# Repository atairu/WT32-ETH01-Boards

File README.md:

KiCAD files for WT32-ETH01 MCU breakout board PCBs. PCBs includes

* 1-Port with USB 2.0 receptacle
* 1-Port with USB type C receptacle
* 2-Port with USB 2.0 receptacle
* 4-Port with USB 2.0 receptacle
* 8-Port with USB 2.0 receptacle

The boards feature multi voltage on the input between 5v - 24v and can be used to program WT32-ETH01 using on-board serial to UART protocol IC with WLED.

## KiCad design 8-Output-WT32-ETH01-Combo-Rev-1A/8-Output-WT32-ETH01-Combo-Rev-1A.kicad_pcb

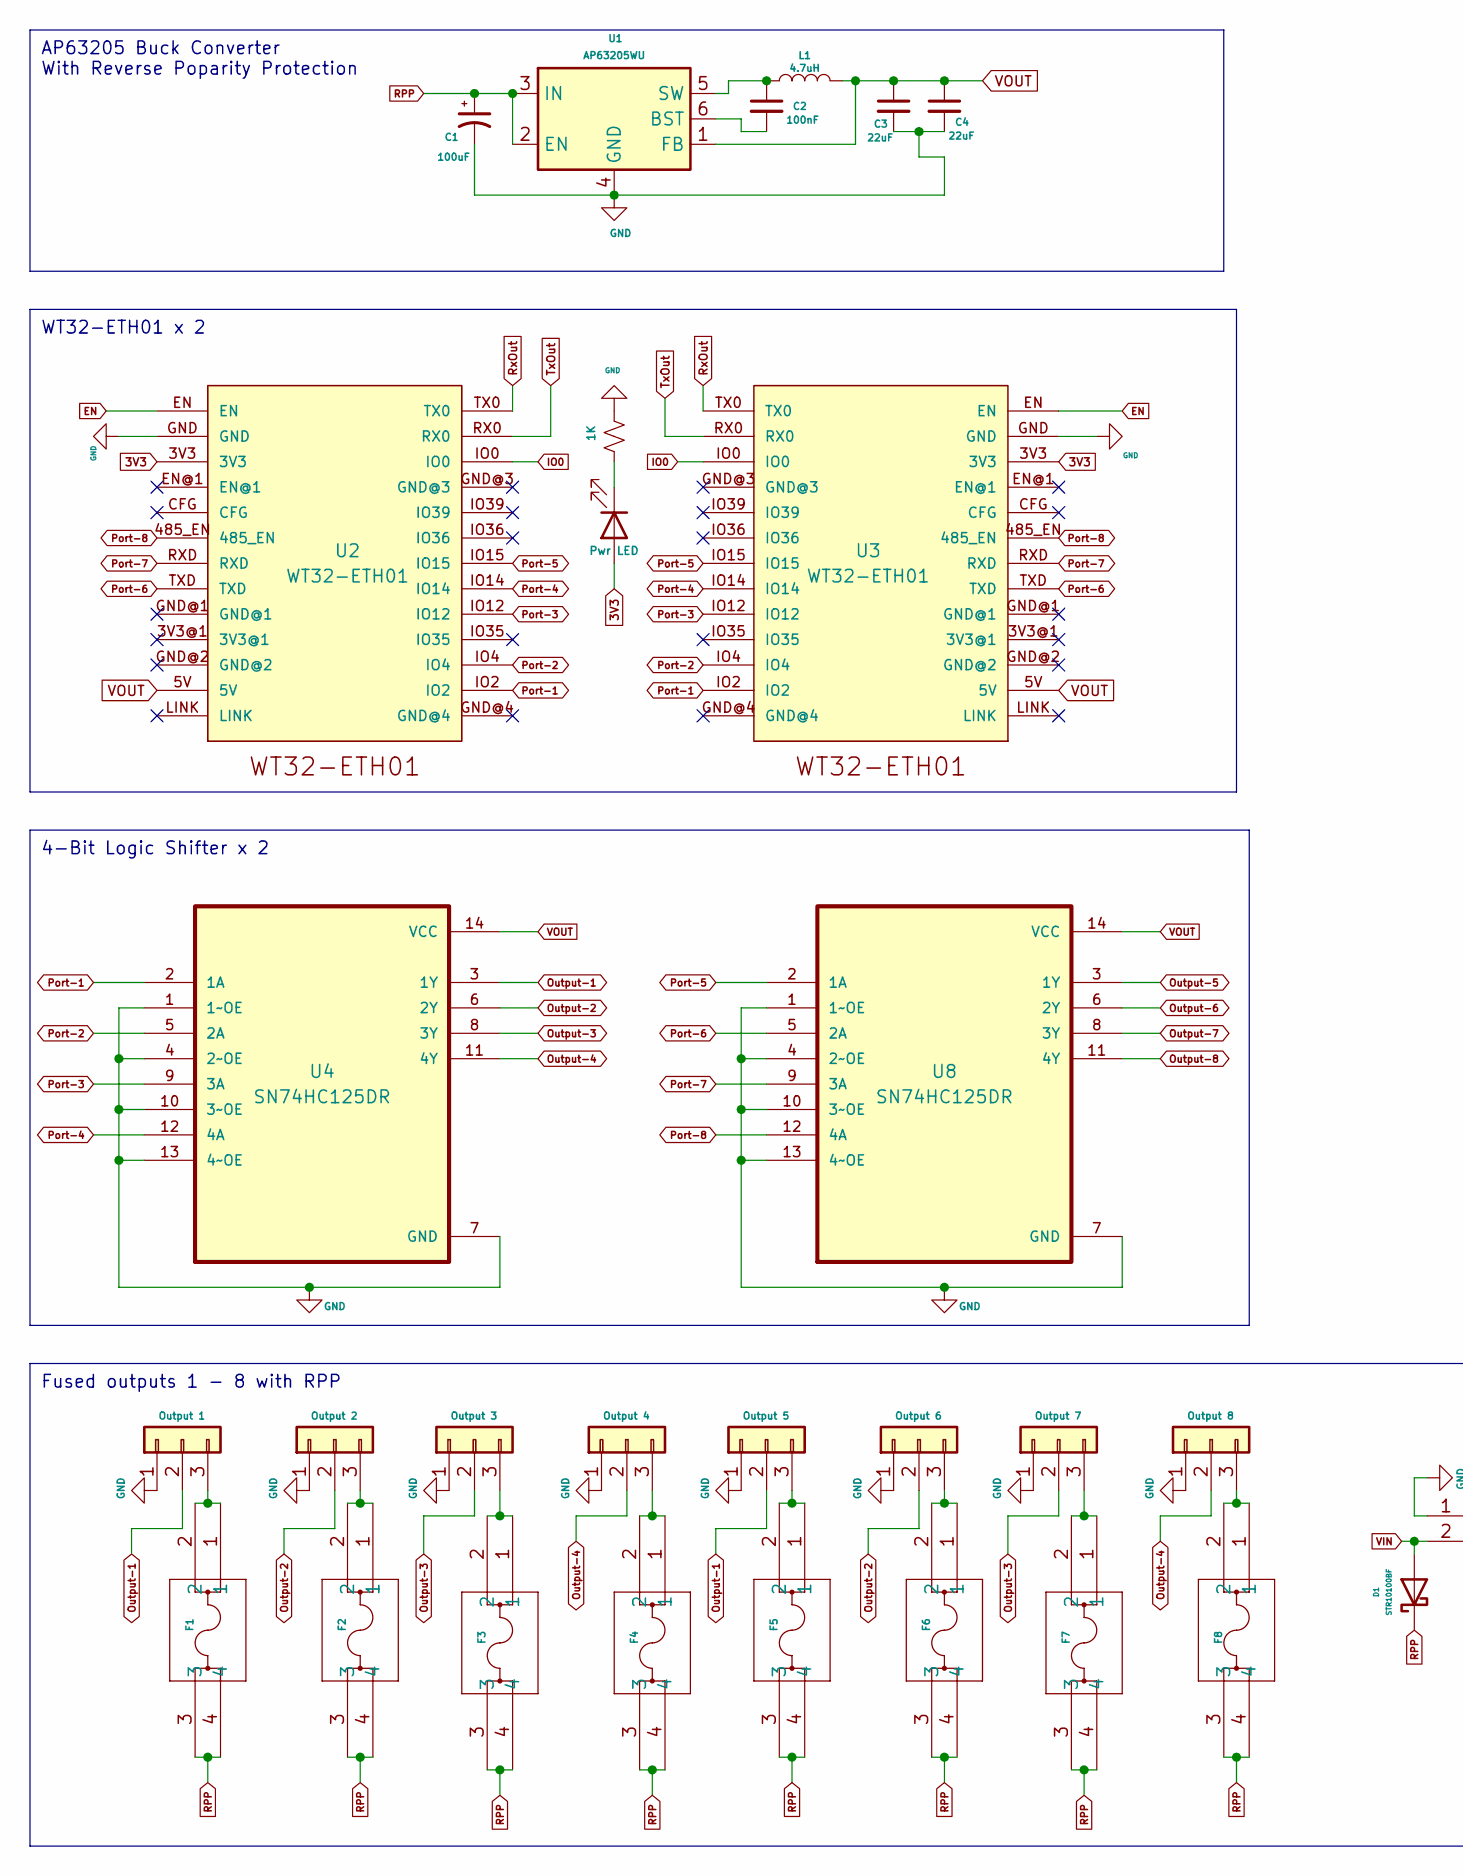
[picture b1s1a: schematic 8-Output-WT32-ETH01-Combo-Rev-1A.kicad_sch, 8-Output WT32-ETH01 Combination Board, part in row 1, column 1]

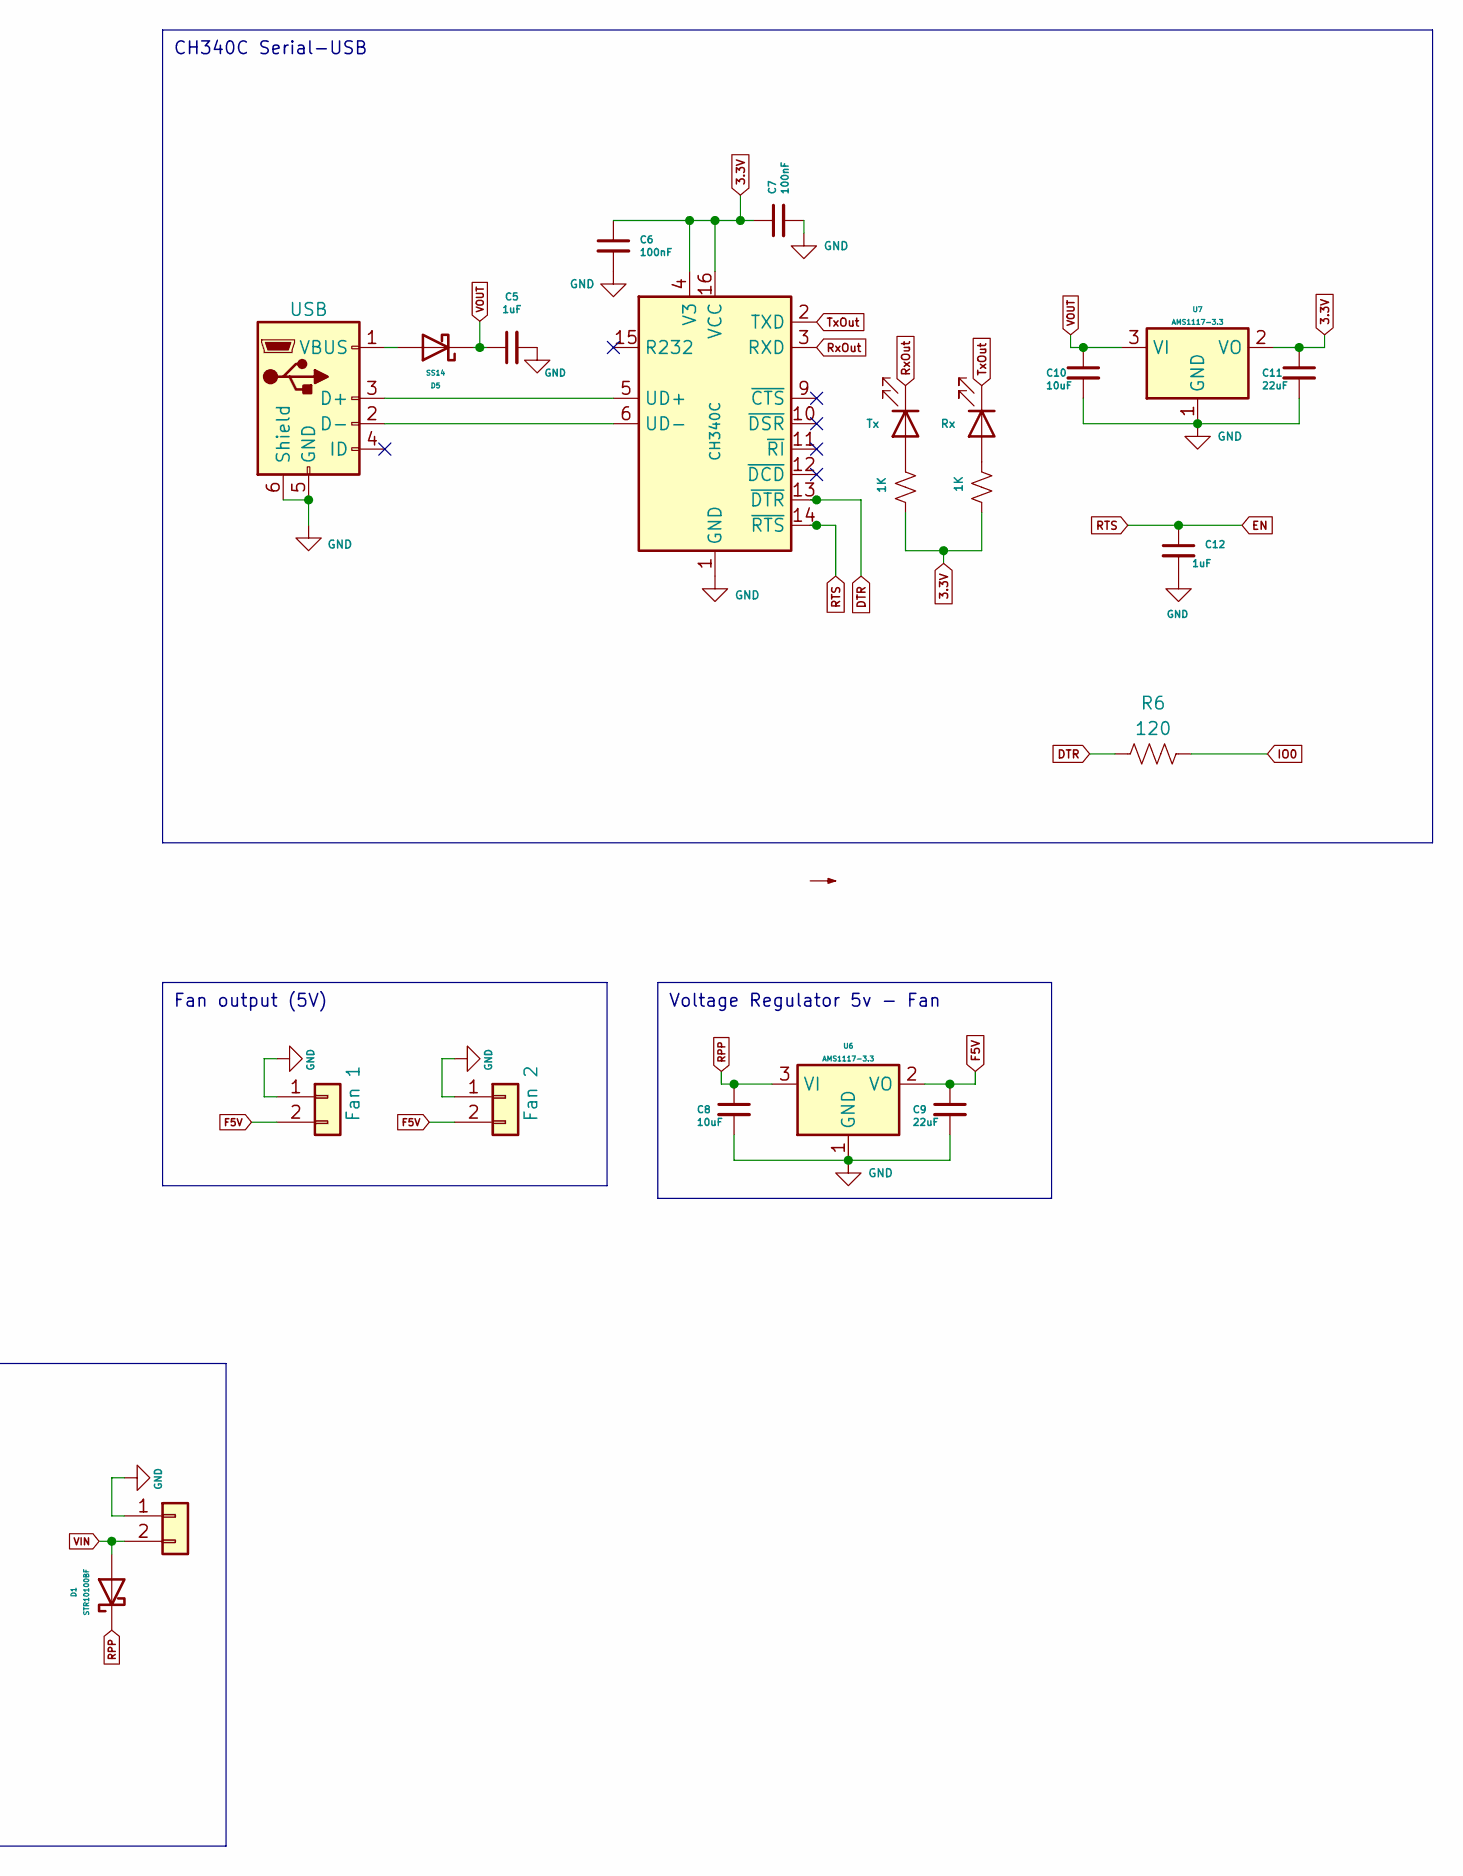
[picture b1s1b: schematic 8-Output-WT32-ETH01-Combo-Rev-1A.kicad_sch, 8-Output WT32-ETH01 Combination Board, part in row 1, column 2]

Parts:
C1: 100uF; CP_Elec_6.3x5.4
C2, C6, C7: 100nF; C_0805_2012Metric_Pad1.18x1.45mm_HandSolder
C3, C4, C9, C11: 22uF; C_0805_2012Metric_Pad1.18x1.45mm_HandSolder
C5, C12: 1uF; C_0805_2012Metric_Pad1.18x1.45mm_HandSolder
C8, C10: 10uF; C_0805_2012Metric_Pad1.18x1.45mm_HandSolder
D1: STR10100BF; D_SMB_Handsoldering
D2: Pwr LED; LED_0805_2012Metric_Pad1.15x1.40mm_HandSolder
D3: Tx; LED_0805_2012Metric_Pad1.15x1.40mm_HandSolder
D4: Rx; LED_0805_2012Metric_Pad1.15x1.40mm_HandSolder
D5: SS14; D_SOD-323_HandSoldering
F1, F2, F3, F4, F5, F6, F7, F8: MCCQ-122_MTC
J1: 4.5-28V Power Input; 1714955
J2: USB; USB_Micro-B_Unknown_5s_SMT
J3: Fan 1; JST_XH_B2B-XH-A_1x02_P2.50mm_Vertical
J4: Fan 2; JST_XH_B2B-XH-A_1x02_P2.50mm_Vertical
JST1: Output 1; TerminalBlock_Phoenix_MKDS-1,5-3-5.08_1x03_P5.08mm_Horizont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
JST2: Output 2; TerminalBlock_Phoenix_MKDS-1,5-3-5.08_1x03_P5.08mm_Horizont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
JST3: Output 3; TerminalBlock_Phoenix_MKDS-1,5-3-5.08_1x03_P5.08mm_Horizont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
JST4: Output 4; TerminalBlock_Phoenix_MKDS-1,5-3-5.08_1x03_P5.08mm_Horizont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
JST5: Output 5; TerminalBlock_Phoenix_MKDS-1,5-3-5.08_1x03_P5.08mm_Horizont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
JST6: Output 6; TerminalBlock_Phoenix_MKDS-1,5-3-5.08_1x03_P5.08mm_Horizont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
JST7: Output 7; TerminalBlock_Phoenix_MKDS-1,5-3-5.08_1x03_P5.08mm_Horizont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
JST8: Output 8; TerminalBlock_Phoenix_MKDS-1,5-3-5.08_1x03_P5.08mm_Horizont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
L1: 4.7uH; L_Taiyo-Yuden_MD-5050
R1, R2, R3: 1K; R_0805_2012Metric_Pad1.20x1.40mm_HandSolder
R6: 120; R_0805_2012Metric_Pad1.20x1.40mm_HandSolder
U1: AP63205WU; TSOT-23-6
U2, U3: WT32-ETH01; WT32_ETH01
U4, U8: SN74HC125DR; SOIC127P600X175-14N
U5: CH340C; SOP-16_3.9x9.9mm_P1.27mm
U6, U7: AMS1117-3.3; SOT-223-3_TabPin2

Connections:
3.3V: C6.1, C7.1, C11.1, R2.1, R3.2, U5.4 (V3), U5.16 (VCC), U7.2 (VO)
3V3: D2.2 (A), U2.3V3, U3.3V3
DTR: R6.1, U5.13 (~DTR)
EN: C12.1, U2.EN, U3.EN, U5.14 (~RTS)
F5V: C9.1, J3.2, J4.2, U6.2 (VO)
GND: C1.2, C3.2, C4.2, C5.2, C6.2, C7.2, C8.2, C9.2, C10.2, C11.2, C12.2, J1.1, J2.5 (GND), J2.6 (Shield), J3.1, J4.1, JST1.1, JST2.1, JST3.1, JST4.1, JST5.1, JST6.1, JST7.1, JST8.1, R1.1, U1.4 (GND), U2.GND, U3.GND, U4.1 (1~OE), U4.4 (2~OE), U4.7 (GND), U4.10 (3~OE), U4.13 (4~OE), U5.1 (GND), U6.1 (GND), U7.1 (GND), U8.1 (1~OE), U8.4 (2~OE), U8.7 (GND), U8.10 (3~OE), U8.13 (4~OE)
IO0: R6.2, U2.IO0, U3.IO0
unnamed: D2.1 (K), R1.2
unnamed: D3.2 (A), R2.2
unnamed: D4.2 (A), R3.1
unnamed: D5.2 (A), J2.1 (VBUS)
unnamed: J2.3 (D+), U5.5 (UD+)
unnamed: J2.2 (D-), U5.6 (UD-)
unnamed: F1.1, F1.2, JST1.3
unnamed: F2.1, F2.2, JST2.3
unnamed: F3.1, F3.2, JST3.3
unnamed: F4.1, F4.2, JST4.3
unnamed: F5.1, F5.2, JST5.3
unnamed: F6.1, F6.2, JST6.3
unnamed: F7.1, F7.2, JST7.3
unnamed: F8.1, F8.2, JST8.3
unnamed: C2.2, U1.6 (BST)
unnamed: C2.1, L1.1, U1.5 (SW)
Output-1: JST1.2, JST5.2, U4.3 (1Y)
Output-2: JST2.2, JST6.2, U4.6 (2Y)
Output-3: JST3.2, JST7.2, U4.8 (3Y)
Output-4: JST4.2, JST8.2, U4.11 (4Y)
Output-5: U8.3 (1Y)
Output-6: U8.6 (2Y)
Output-7: U8.8 (3Y)
Output-8: U8.11 (4Y)
Port-1: U2.IO2, U3.IO2, U4.2 (1A)
Port-2: U2.IO4, U3.IO4, U4.5 (2A)
Port-3: U2.IO12, U3.IO12, U4.9 (3A)
Port-4: U2.IO14, U3.IO14, U4.12 (4A)
Port-5: U2.IO15, U3.IO15, U8.2 (1A)
Port-6: U2.TXD, U3.TXD, U8.5 (2A)
Port-7: U2.RXD, U3.RXD, U8.9 (3A)
Port-8: U2.485_EN, U3.485_EN, U8.12 (4A)
RPP: C1.1, C8.1, D1.1 (K), F1.3, F1.4, F2.3, F2.4, F3.3, F3.4, F4.3, F4.4, F5.3, F5.4, F6.3, F6.4, F7.3, F7.4, F8.3, F8.4, U1.2 (EN), U1.3 (IN), U6.3 (VI)
RxOut: D3.1 (K), U2.TX0, U3.TX0, U5.3 (RXD)
TxOut: D4.1 (K), U2.RX0, U3.RX0, U5.2 (TXD)
VIN: D1.2 (A), J1.2
VOUT: C3.1, C4.1, C5.1, C10.1, D5.1 (K), L1.2, U1.1 (FB), U2.5V, U3.5V, U4.14 (VCC), U7.3 (VI), U8.14 (VCC)

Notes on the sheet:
AP63205 Buck Converter With Reverse Poparity Protection
4-Bit Logic Shifter x 2
Voltage Regulator 5v - Fan
CH340C Serial-USB
WT32-ETH01 x 2
Fused outputs 1 - 8 with RPP
Fan output (5V)

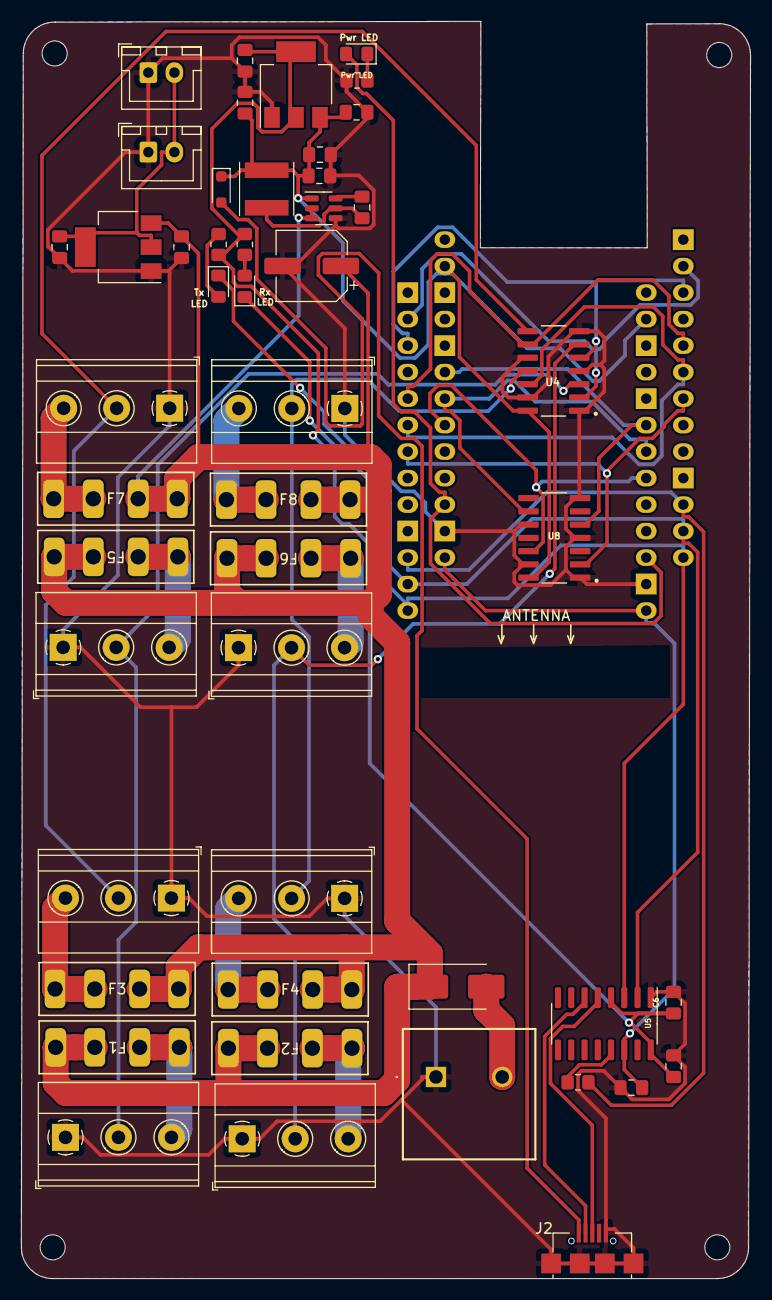
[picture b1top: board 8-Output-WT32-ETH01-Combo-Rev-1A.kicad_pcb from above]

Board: 2 copper layers, 69.9 x 120.5 mm, 50 parts (1 on the bottom side), 40 nets.
